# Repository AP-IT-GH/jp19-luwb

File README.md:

# Internet Of Things - *Location Ultra Wide Band*

## Angular

## API

**Teammembers**
* Hector Brasfalean
* Davy Cools
* Jens Peeters

## Summary
*Het lokaliseren van een robot/drone (indoor) door middel van Ultra Wide Band technologie. Dit gaan we visueel weergeven. We zullen de robot/drone ook op een autonome manier kunnen verplaatsen.*

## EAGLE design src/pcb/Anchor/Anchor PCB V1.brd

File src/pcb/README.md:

# PCB

In deze map verzamel je op een gestructueerde manier de bron bestanden voor het
PCB ontwerp.

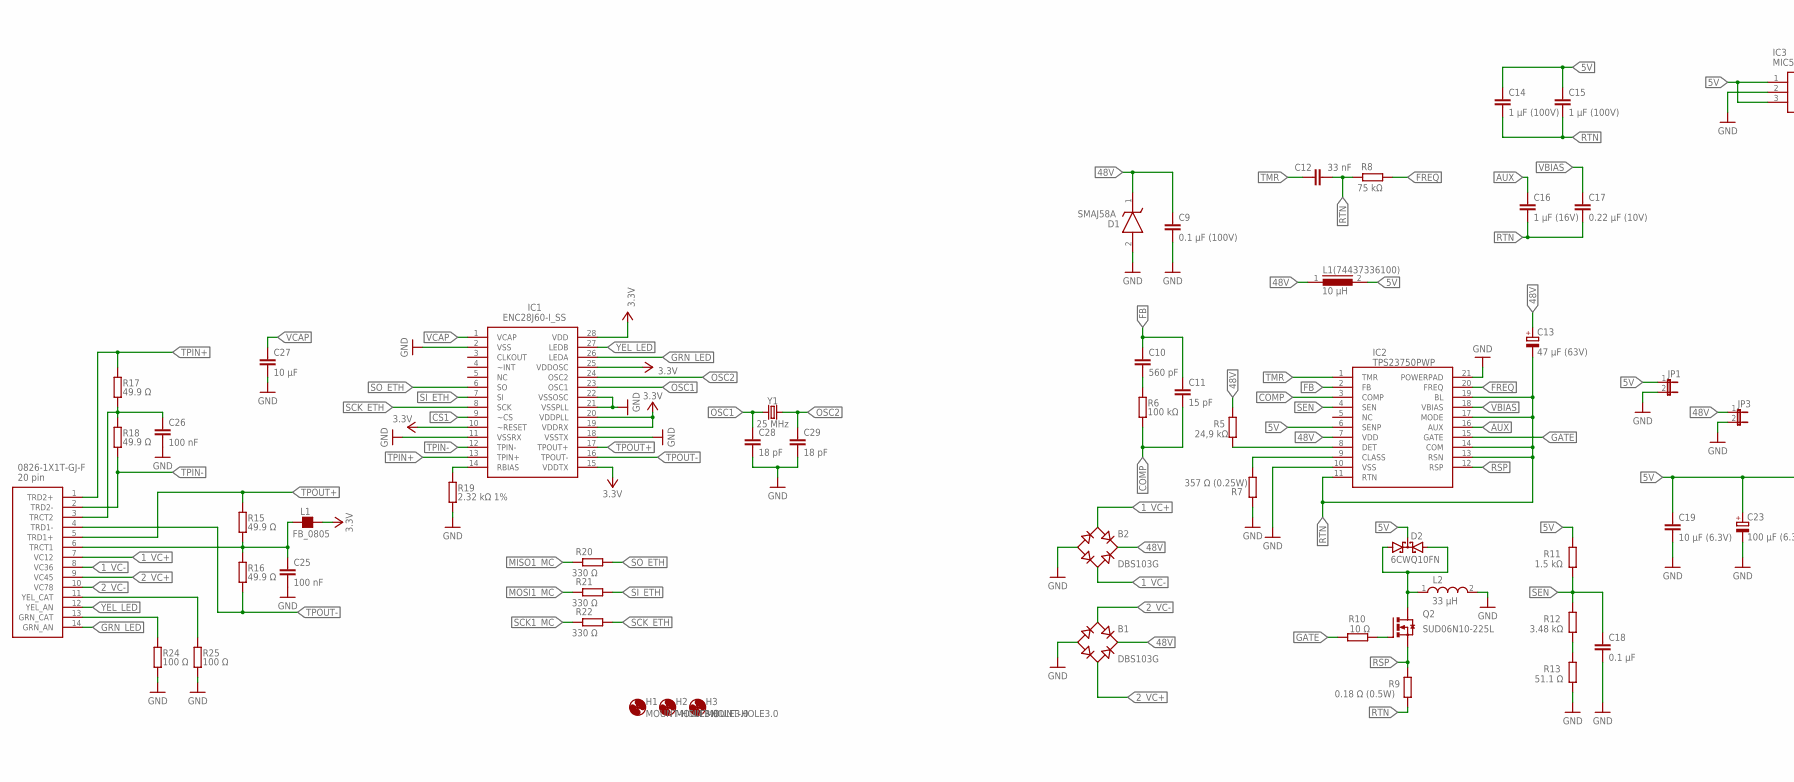
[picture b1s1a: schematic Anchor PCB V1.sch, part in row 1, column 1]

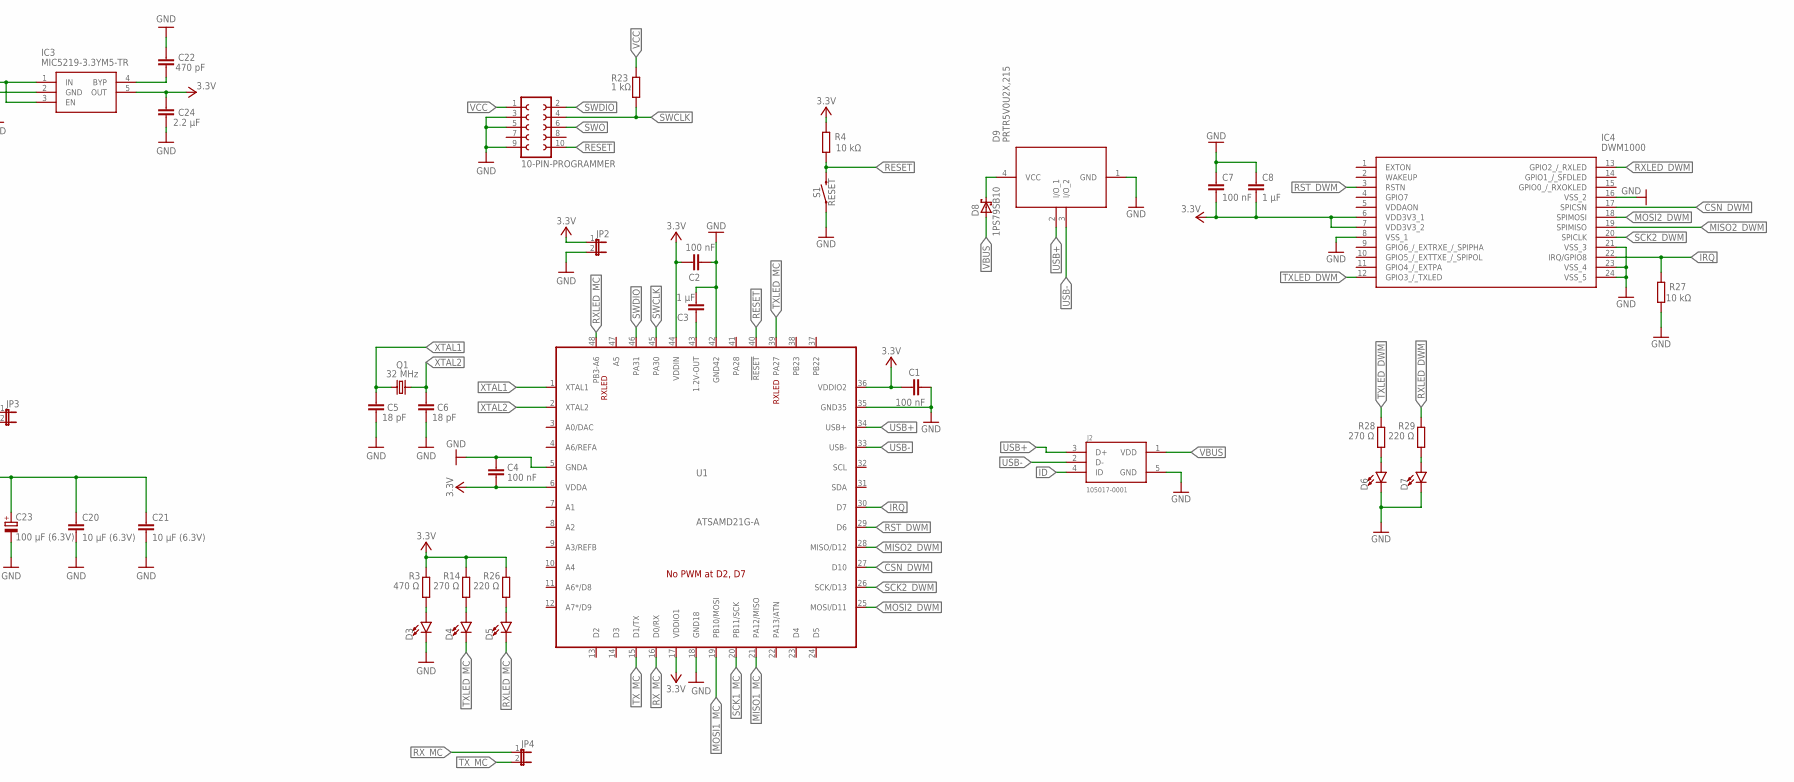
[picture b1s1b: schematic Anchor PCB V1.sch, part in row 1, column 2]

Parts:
10-PIN-PROGRAMMER: FE05-2
B1, B2: DBS103G; DBS
C1, C2, C4, C7, C25, C26: 100 nF; C0805
C3, C8: 1 µF; C0805
C5, C6, C28, C29: 18 pF; C0805
C9: 0.1 µF (100V); C0805
C10: 560 pF; C0805
C11: 15 pF; C0805
C12: 33 nF; C0805
C13: 47 µF (63V); E3,5-8
C14, C15: 1 µF (100V); C0805
C16: 1 µF (16V); C0805
C17: 0.22 µF (10V); C0805
C18: 0.1 µF; C0805
C19, C20, C21: 10 µF (6.3V); C0805
C22: 470 pF; C0805
C23: 100 µF (6.3V); UD-6,3X7,7_NICHICON
C24: 2.2 µF; C0805
C27: 10 µF; C0805
D1: SMAJ58A; DIOM5026X229N
D2: 6CWQ10FN; DPAK
D3: POWER; CHIP-LED0805
D4, D6: TX; CHIP-LED0805
D5, D7: RX; CHIP-LED0805
D8: 1PS79SB10; SOD523
D9: PRTR5V0U2X,215; SOT-143B
H1, H2, H3: MOUNT-HOLE3.0; 3,0
IC1: ENC28J60-I_SS; SOP65P780X200-28N
IC2: TPS23750PWP; SOP65P640X120-21N
IC3: MIC5219-3.3YM5-TR; SOT95P280X130-5N
IC4: DWM1000
J1: 0826-1X1T-GJ-F
J2: 105017-0001; MOLEX_105017-0001
JP1, JP2, JP3, JP4: JP1E; JP1
L1: FB_0805; L0805
L1(74437336100): 10 µH; DR73
L2: 33 µH; WE-PD_1260/1245/1280/1210
Q1: 32 MHz; ABS07
Q2: SUD06N10-225L; SOT223
R3: 470 Ω; R0805
R4, R27: 10 kΩ; M0805
R5: 24,9 kΩ; R0805
R6: 100 kΩ; R0805
R7: 357 Ω (0.25W); R0805
R8: 75 kΩ; R0805
R9: 0.18 Ω (0.5W); R2010
R10: 10 Ω; R0805
R11: 1.5 kΩ; R0805
R12: 3.48 kΩ; R0805
R13: 51.1 Ω; R0805
R14, R28: 270 Ω; R0805
R15, R16, R17, R18: 49.9 Ω; R0805
R19: 2.32 kΩ 1%; R0805
R20, R21, R22: 330 Ω; R0805
R23: 1 kΩ; R0805
R24, R25: 100 Ω; R0805
R26, R29: 220 Ω; R0805
S1: RESET; TACTILE_SWITCH_SMD_4.5MM
U1: ATSAMD21G-A; TQFP-48
Y1: 25 MHz; HC49UP

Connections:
1_VC+: B2.AC1, J1.7 (VC12)
1_VC-: B2.AC2, J1.8 (VC36)
2_VC+: B1.AC2, J1.9 (VC45)
2_VC-: B1.AC1, J1.10 (VC78)
5V: C14.1, C15.1, C19.1, C20.1, C21.1, C23.+, D2.4 (C), IC2.6 (SENP), IC3.1 (IN), IC3.3 (EN), JP1.1, L1(74437336100).2, R11.2
48V: B1.+, B2.+, C9.1, C13.+, D1.1 (K), IC2.7 (VDD), JP3.1, L1(74437336100).1, R5.2
AUX: C16.1, IC2.16 (AUX)
COMP: C11.2, IC2.3 (COMP), R6.2
COM_A_SHTKY: D2.1 (A1), D2.3 (A2), L2.1, Q2.4 (D)
CS1: IC1.9 (~CS)
CSN_DWM: IC4.17 (SPICSN), U1.27 (D10)
FB: C10.1, C11.1, IC2.2 (FB)
FREQ: IC2.20 (FREQ), R8.2
GATE: IC2.15 (GATE), R10.1
GND: 10-PIN-PROGRAMMER.3, 10-PIN-PROGRAMMER.5, 10-PIN-PROGRAMMER.9, B1.-, B2.-, C1.2, C2.2, C3.2, C4.2, C5.2, C6.2, C7.1, C8.1, C9.2, C18.2, C19.2, C20.2, C21.2, C22.1, C23.-, C24.2, C25.2, C26.2, C27.2, C28.2, C29.2, D1.2 (A), D3.C, D6.C, D7.C, D9.1 (GND), IC1.2 (VSS), IC1.11 (VSSRX), IC1.18 (VSSTX), IC1.21 (VSSPLL), IC1.22 (VSSOSC), IC2.10 (VSS), IC2.21 (POWERPAD), IC3.2 (GND), IC4.8 (VSS_1), IC4.16 (VSS_2), IC4.21 (VSS_3), IC4.23 (VSS_4), IC4.24 (VSS_5), J2.5 (GND), JP1.2, JP2.2, JP3.2, L2.2, R7.1, R13.1, R19.2, R24.2, R25.2, R27.1, S1.2 (1), S1.3 (1), U1.5 (GNDA), U1.18 (GND18), U1.35 (GND35), U1.42 (GND42)
GRN_CAT: J1.13 (GRN_CAT), R24.1
GRN_LED: IC1.26 (LEDA), J1.14 (GRN_AN)
ID: J2.4 (ID)
IRQ: IC4.22 (IRQ/GPIO8), R27.2, U1.30 (D7)
MISO1_MC: R20.1, U1.21 (PA12/MISO)
MISO2_DWM: IC4.19 (SPIMISO), U1.28 (MISO/D12)
MOSI1_MC: R21.1, U1.19 (PB10/MOSI)
MOSI2_DWM: IC4.18 (SPIMOSI), U1.25 (MOSI/D11)
unnamed: C3.1, U1.43 (1.2V-OUT)
unnamed: IC2.8 (DET), R5.1
unnamed: IC2.9 (CLASS), R7.2
unnamed: C25.1, J1.6 (TRCT1), L1.1, R15.2, R16.1
unnamed: C10.2, R6.1
unnamed: C26.1, J1.3 (TRCT2), R17.2, R18.1
unnamed: Q2.1 (G), R10.2
unnamed: IC1.14 (RBIAS), R19.1
unnamed: D3.A, R3.1
unnamed: R12.1, R13.2
unnamed: D4.A, R14.1
unnamed: D5.A, R26.1
unnamed: D6.A, R28.1
unnamed: D7.A, R29.1
unnamed: D8.1 (K), D9.4 (VCC)
unnamed: C22.2, IC3.4 (BYP)
OSC1: C28.1, IC1.23 (OSC1), Y1.1
OSC2: C29.1, IC1.24 (OSC2), Y1.2
RESET: 10-PIN-PROGRAMMER.10, R4.1, S1.1 (2), S1.4 (2), U1.40 (!RESET!)
RSP: IC2.12 (RSP), Q2.3 (S), R9.2
RST_DWM: IC4.3 (RSTN), U1.29 (D6)
RTN: C12.2, C13.-, C14.2, C15.2, C16.2, C17.2, IC2.11 (RTN), IC2.13 (RSN), IC2.14 (COM), IC2.17 (MODE), IC2.19 (BL), R8.1, R9.1
RXLED_DWM: IC4.13 (GPIO2_/_RXLED), R29.2
RXLED_MC: D5.C, U1.48 (PB3-A6)
RX_MC: JP4.1, U1.16 (D0/RX)
SCK1_MC: R22.1, U1.20 (PB11/SCK)
SCK2_DWM: IC4.20 (SPICLK), U1.26 (SCK/D13)
SCK_ETH: IC1.8 (SCK), R22.2
SEN: C18.1, IC2.4 (SEN), R11.1, R12.2
SI_ETH: IC1.7 (SI), R21.2
SO_ETH: IC1.6 (SO), R20.2
SWCLK: 10-PIN-PROGRAMMER.4, R23.1, U1.45 (PA30)
SWDIO: 10-PIN-PROGRAMMER.2, U1.46 (PA31)
SWO: 10-PIN-PROGRAMMER.6
TMR: C12.1, IC2.1 (TMR)
TPIN+: IC1.13 (TPIN+), J1.1 (TRD2+), R17.1
TPIN-: IC1.12 (TPIN-), J1.2 (TRD2-), R18.2
TPOUT+: IC1.17 (TPOUT+), J1.5 (TRD1+), R15.1
TPOUT-: IC1.16 (TPOUT-), J1.4 (TRD1-), R16.2
TXLED_DWM: IC4.12 (GPIO3_/_TXLED), R28.2
TXLED_MC: D4.C, U1.39 (PA27)
TX_MC: JP4.2, U1.15 (D1/TX)
USB+: D9.2 (I/O_1), J2.3 (D+), U1.34 (USB+)
USB-: D9.3 (I/O_2), J2.2 (D-), U1.33 (USB-)
VBIAS: C17.1, IC2.18 (VBIAS)
VBUS: D8.2 (A), J2.1 (VDD)
VCAP: C27.1, IC1.1 (VCAP)
VCC: 10-PIN-PROGRAMMER.1, C1.1, C2.1, C4.1, C7.2, C8.2, C24.1, IC1.10 (~RESET), IC1.15 (VDDTX), IC1.19 (VDDRX), IC1.20 (VDDPLL), IC1.25 (VDDOSC), IC1.28 (VDD), IC3.5 (OUT), IC4.6 (VDD3V3_1), IC4.7 (VDD3V3_2), JP2.1, L1.2, R3.2, R4.2, R14.2, R23.2, R26.2, U1.6 (VDDA), U1.17 (VDDIO1), U1.36 (VDDIO2), U1.44 (VDDIN)
XTAL1: C5.1, Q1.2, U1.1 (XTAL1)
XTAL2: C6.1, Q1.1, U1.2 (XTAL2)
YEL_CAT: J1.11 (YEL_CAT), R25.1
YEL_LED: IC1.27 (LEDB), J1.12 (YEL_AN)

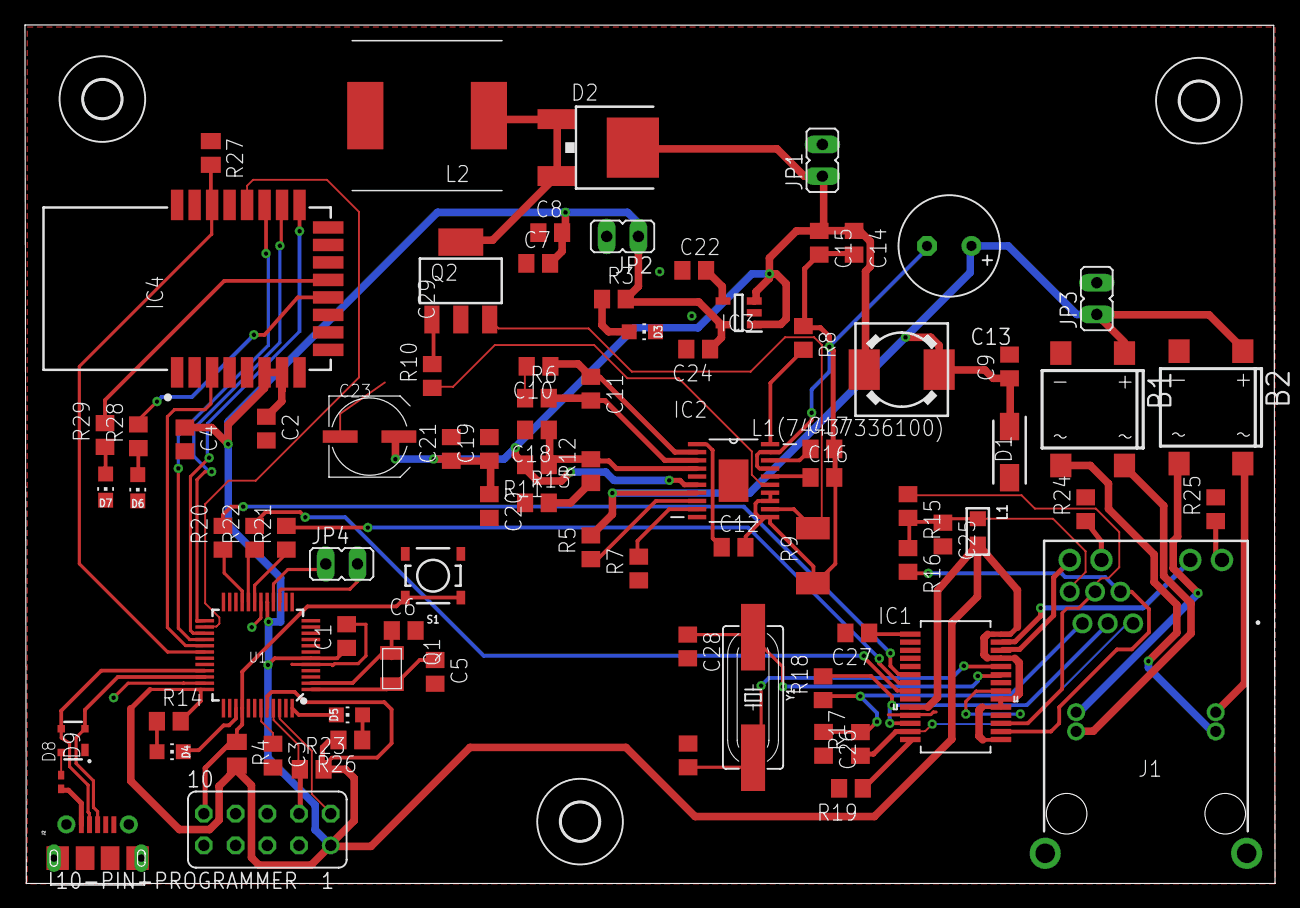
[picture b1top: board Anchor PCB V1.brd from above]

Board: 2 copper layers, 100.1 x 68.7 mm, 89 parts (0 on the bottom side), 72 nets.

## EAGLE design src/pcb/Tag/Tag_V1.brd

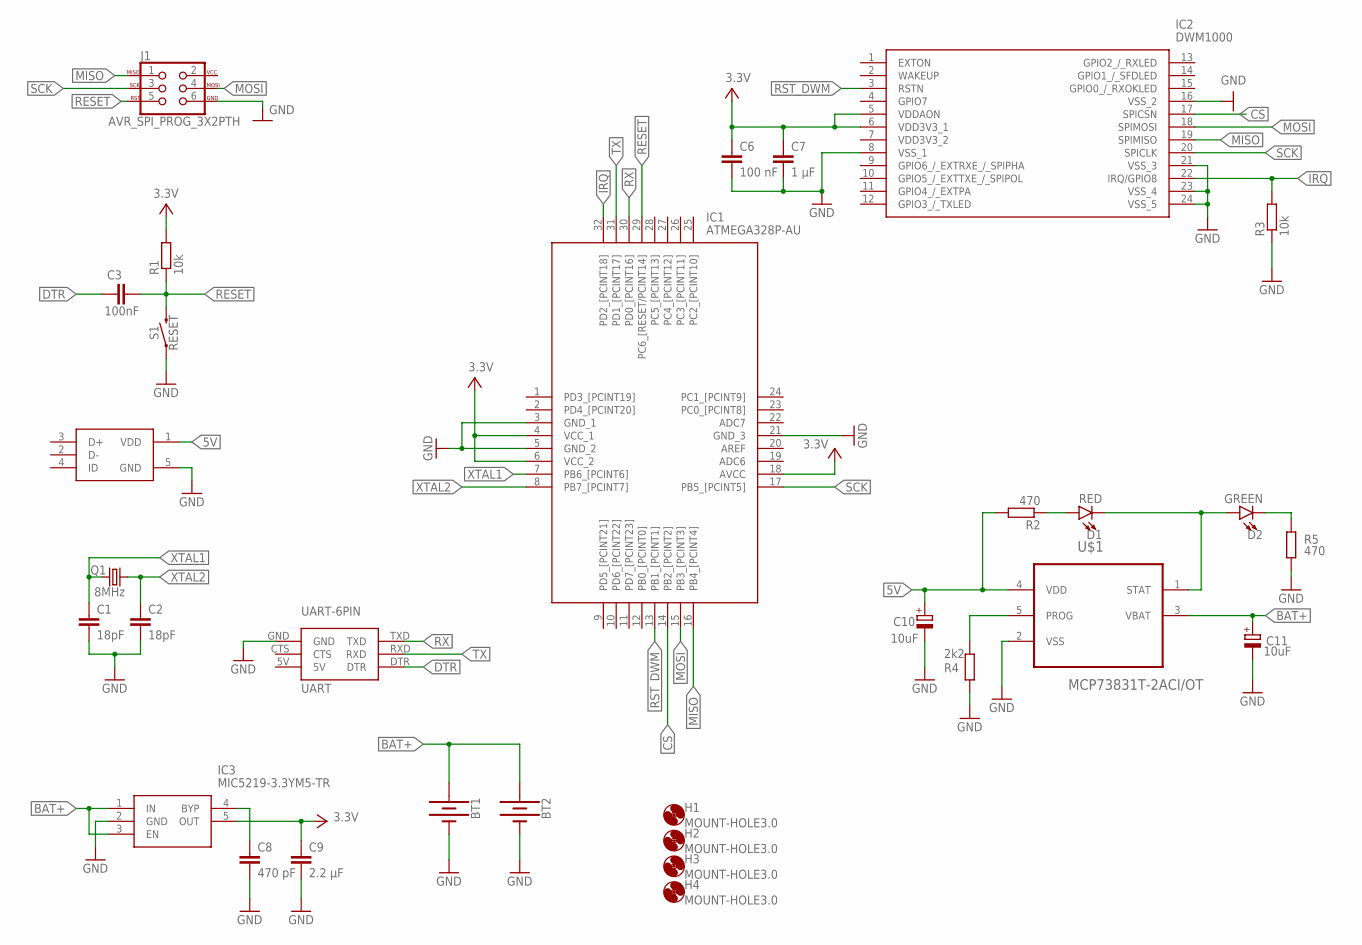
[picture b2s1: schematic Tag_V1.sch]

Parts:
BT1, BT2: BATTERY-18650; BATTERY_18650-HOLDER
C1, C2: 18pF; C0805
C3: 100nF; C0805
C6: 100 nF; C0805
C7: 1 µF; C0805
C8: 470 pF; C0805
C9: 2.2 µF; C0805
C10, C11: 10uF; E2,5-7
D1: RED; LED-1206
D2: GREEN; LED-1206
H1, H2, H3, H4: MOUNT-HOLE3.0; 3,0
IC1: ATMEGA328P-AU; QFP80P900X900X120-32N
IC2: DWM1000
IC3: MIC5219-3.3YM5-TR; SOT95P280X130-5N
J1: AVR_SPI_PROG_3X2PTH; 2X3
Q1: 8MHz; HC49UP
R1, R3: 10k; R0805
R2, R5: 470; R0805
R4: 2k2; R0805
S1: RESET; TACTILE_SWITCH_PTH_6.0MM
U1: 105017-0001; MOLEX_105017-0001
U$1: MCP73831T-2ACI/OT; SOT95P280X145-5N
U$2: UART-6PIN

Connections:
3.3V: C6.1, C7.1, C9.1, IC1.4 (VCC_1), IC1.6 (VCC_2), IC1.18 (AVCC), IC2.5 (VDDAON), IC2.6 (VDD3V3_1), IC3.5 (OUT), R1.2
5V: C10.+, R2.2, U1.1 (VDD), U$1.4 (VDD)
BAT+: BT1.PWR@1 (+), BT2.PWR@1 (+), C11.+, IC3.1 (IN), IC3.3 (EN), U$1.3 (VBAT)
CS: IC1.14 (PB2_[PCINT2]), IC2.17 (SPICSN)
DTR: C3.1, U$2.DTR
GND: BT1.GND@1 (-), BT2.GND@1 (-), C1.2, C2.2, C6.2, C7.2, C8.2, C9.2, C10.-, C11.-, IC1.3 (GND_1), IC1.5 (GND_2), IC1.21 (GND_3), IC2.8 (VSS_1), IC2.16 (VSS_2), IC2.21 (VSS_3), IC2.23 (VSS_4), IC2.24 (VSS_5), IC3.2 (GND), J1.6, R3.1, R4.2, R5.2, S1.1, U1.5 (GND), U$1.2 (VSS), U$2.GND
IRQ: IC1.32 (PD2_[PCINT18]), IC2.22 (IRQ/GPIO8), R3.2
MISO: IC1.16 (PB4_[PCINT4]), IC2.19 (SPIMISO), J1.1
MOSI: IC1.15 (PB3_[PCINT3]), IC2.18 (SPIMOSI), J1.4
unnamed: D1.C, D2.A, U$1.1 (STAT)
unnamed: D1.A, R2.1
unnamed: C8.1, IC3.4 (BYP)
unnamed: D2.C, R5.1
unnamed: R4.1, U$1.5 (PROG)
RESET: C3.2, IC1.29 (PC6_[RESET/PCINT14]), J1.5, R1.1, S1.3 (2)
RST_DWM: IC1.13 (PB1_[PCINT1]), IC2.3 (RSTN)
RX: IC1.30 (PD0_[PCINT16]), U$2.TXD
SCK: IC1.17 (PB5_[PCINT5]), IC2.20 (SPICLK), J1.3
TX: IC1.31 (PD1_[PCINT17]), U$2.RXD
XTAL1: C1.1, IC1.7 (PB6_[PCINT6]), Q1.1
XTAL2: C2.1, IC1.8 (PB7_[PCINT7]), Q1.2

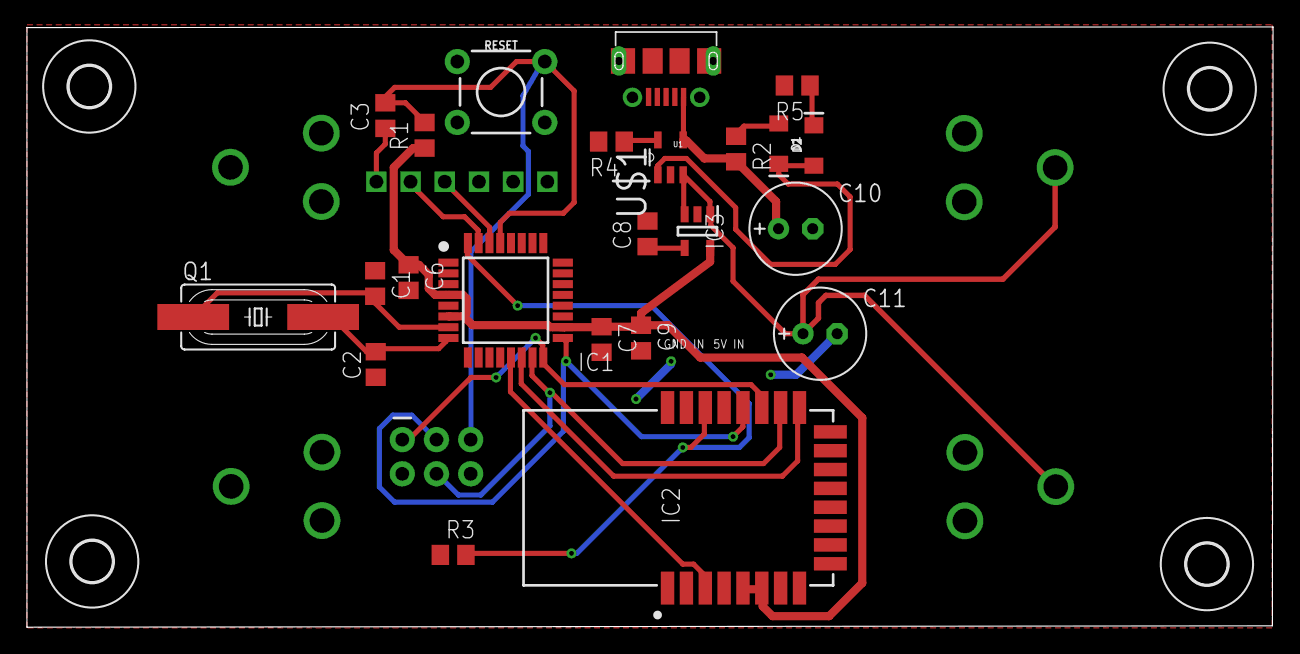
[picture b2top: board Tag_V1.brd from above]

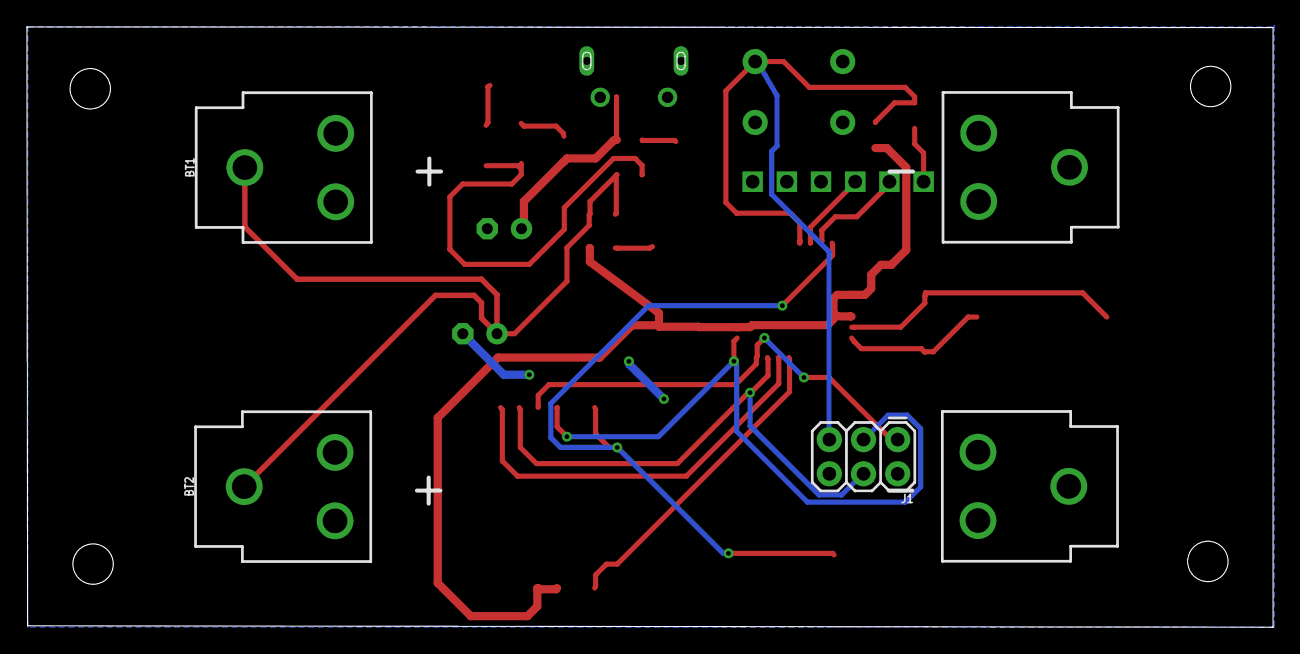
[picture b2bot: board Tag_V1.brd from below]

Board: 2 copper layers, 92.6 x 44.6 mm, 31 parts (3 on the bottom side), 21 nets.

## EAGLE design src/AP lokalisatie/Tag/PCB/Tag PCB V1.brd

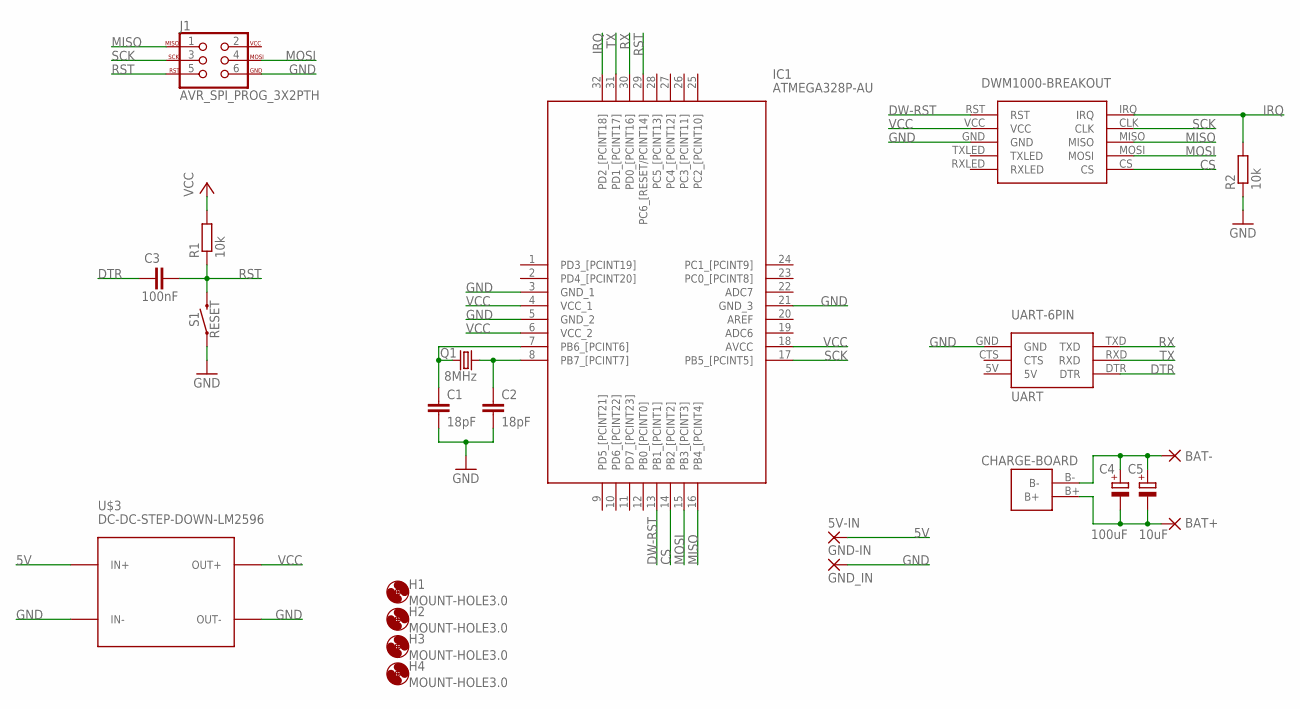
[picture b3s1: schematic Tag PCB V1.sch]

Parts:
5V-IN: 2,15/1,0
BAT+: 2,15/1,0
BAT-: 2,15/1,0
C1, C2: 18pF; C0805
C3: 100nF; C0805
C4: 100uF; E3,5-8
C5: 10uF; E2,5-7
GND-IN: GND_IN; 2,15/1,0
H1, H2, H3, H4: MOUNT-HOLE3.0; 3,0
IC1: ATMEGA328P-AU; QFP80P900X900X120-32N
J1: AVR_SPI_PROG_3X2PTH; 2X3
Q1: 8MHz; HC49UP
R1, R2: 10k; R0805
S1: RESET; TACTILE_SWITCH_PTH_6.0MM
U$1: DWM1000-BREAKOUT
U$2: UART-6PIN
U$3: DC-DC-STEP-DOWN-LM2596
U$4: 18650-CHARGE-5V-OUT

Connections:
5V: 5V-IN.1, U$3.IN+
CS: IC1.14 (PB2_[PCINT2]), U$1.CS
DTR: C3.1, U$2.DTR
DW-RST: IC1.13 (PB1_[PCINT1]), U$1.RST
GND: C1.2, C2.2, GND-IN.1, IC1.3 (GND_1), IC1.5 (GND_2), IC1.21 (GND_3), J1.6, R2.1, S1.1, U$1.GND, U$2.GND, U$3.IN-, U$3.OUT-
IRQ: IC1.32 (PD2_[PCINT18]), R2.2, U$1.IRQ
MISO: IC1.16 (PB4_[PCINT4]), J1.1, U$1.MISO
MOSI: IC1.15 (PB3_[PCINT3]), J1.4, U$1.MOSI
unnamed: BAT-.1, C4.+, C5.+, U$4.B-
unnamed: BAT+.1, C4.-, C5.-, U$4.B+
unnamed: C2.1, IC1.8 (PB7_[PCINT7]), Q1.2
unnamed: C1.1, IC1.7 (PB6_[PCINT6]), Q1.1
RST: C3.2, IC1.29 (PC6_[RESET/PCINT14]), J1.5, R1.1, S1.3 (2)
RX: IC1.30 (PD0_[PCINT16]), U$2.TXD
SCK: IC1.17 (PB5_[PCINT5]), J1.3, U$1.CLK
TX: IC1.31 (PD1_[PCINT17]), U$2.RXD
VCC: IC1.4 (VCC_1), IC1.6 (VCC_2), IC1.18 (AVCC), R1.2, U$1.VCC, U$3.OUT+

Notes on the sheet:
CHARGE-BOARD

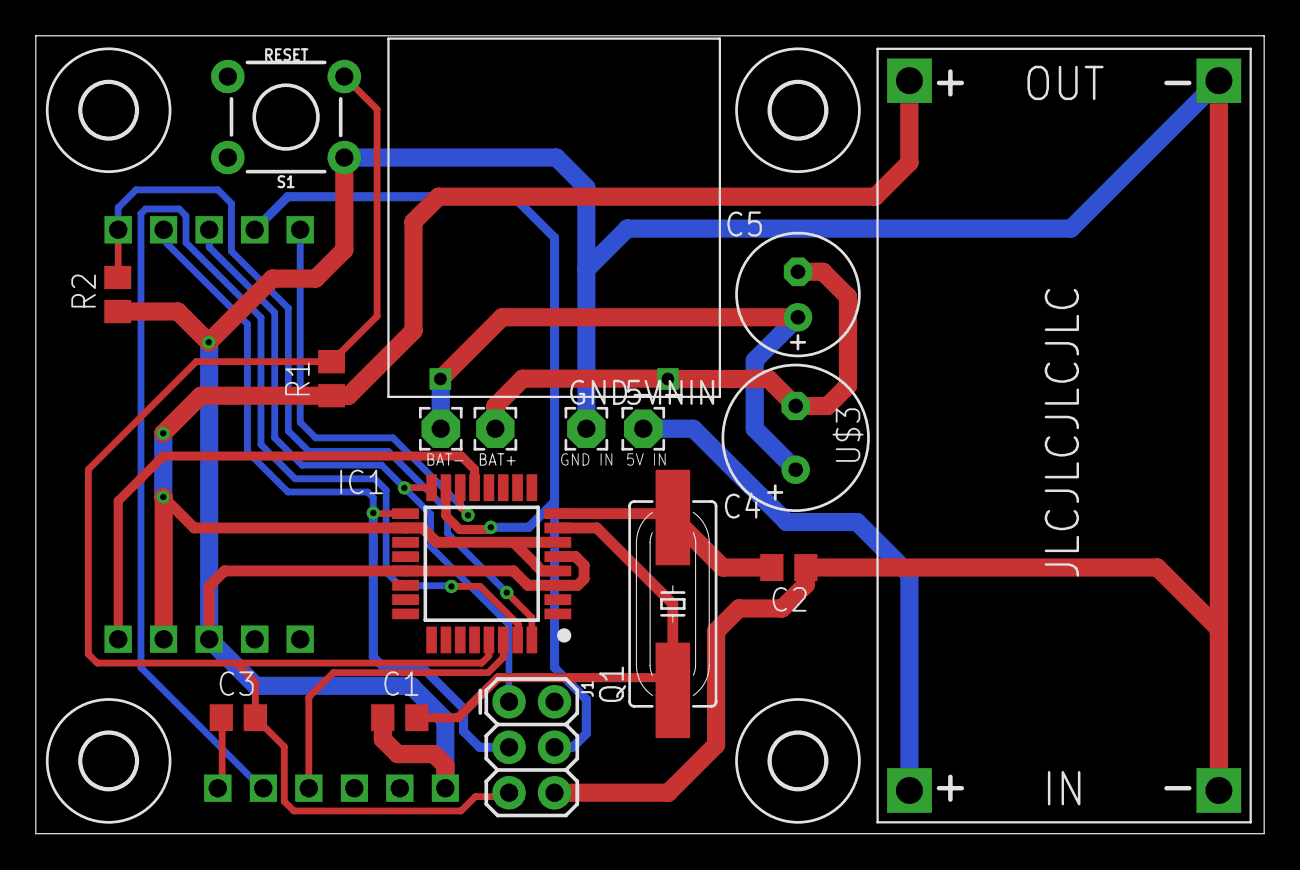
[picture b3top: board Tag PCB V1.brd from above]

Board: 2 copper layers, 68.6 x 44.5 mm, 23 parts (0 on the bottom side), 17 nets.

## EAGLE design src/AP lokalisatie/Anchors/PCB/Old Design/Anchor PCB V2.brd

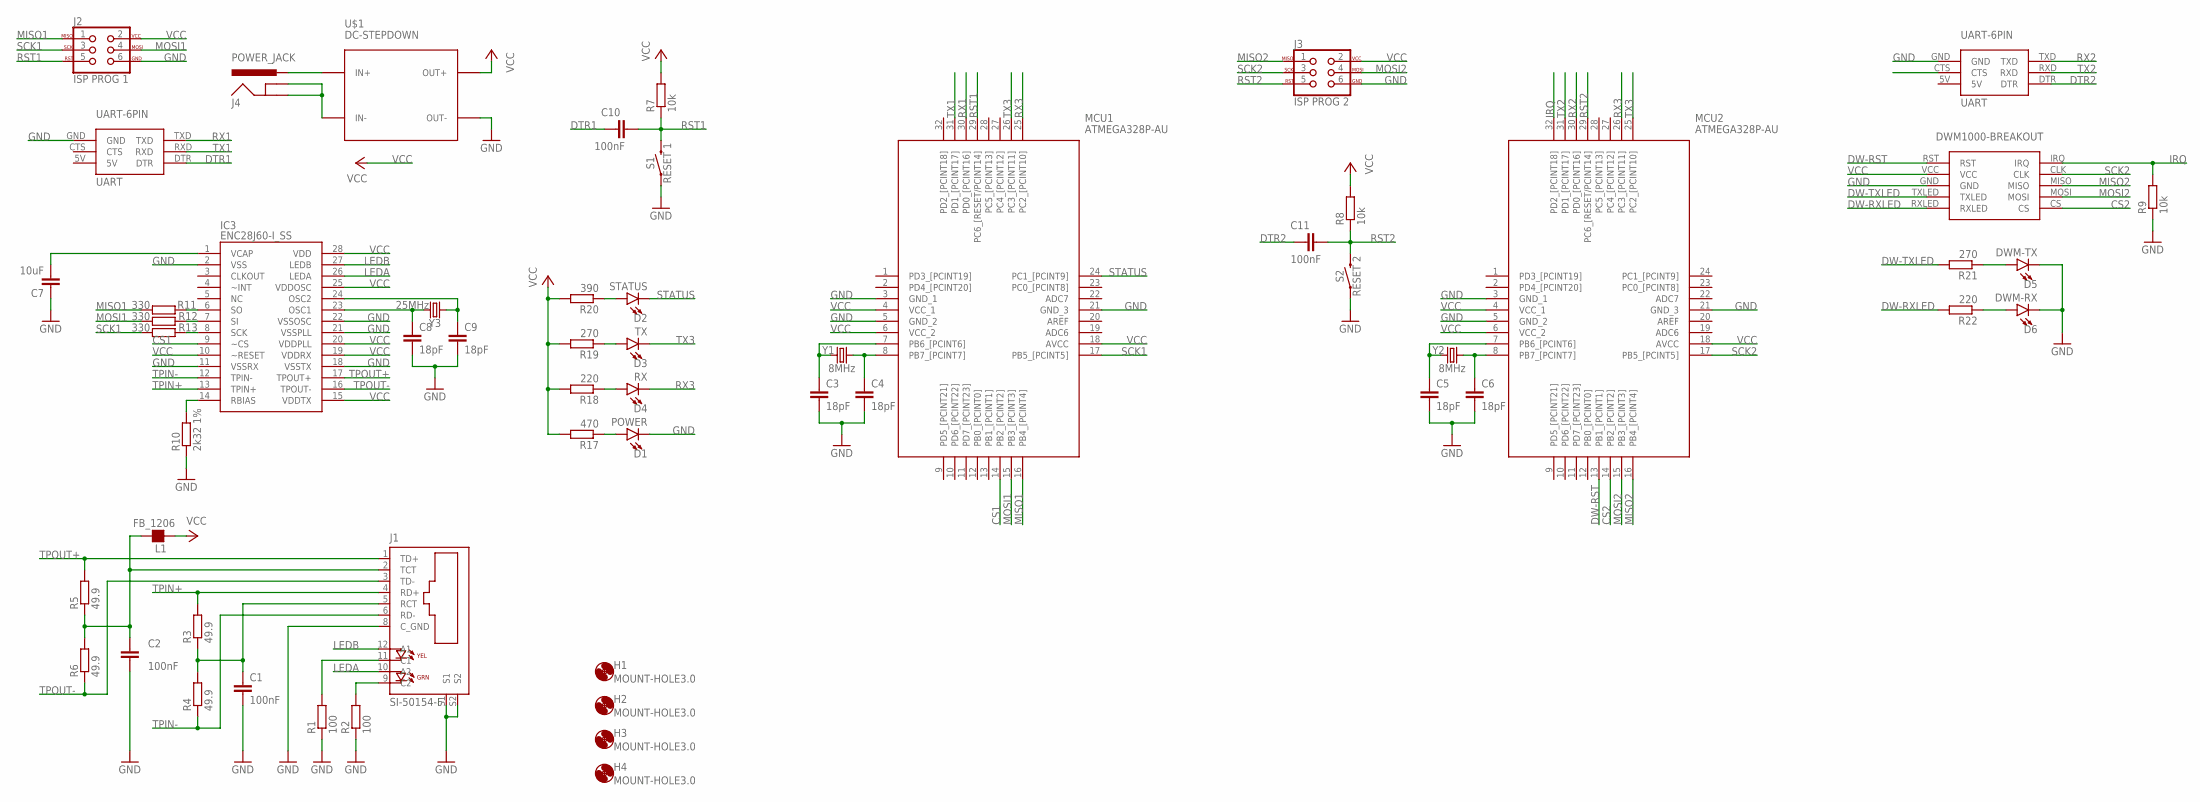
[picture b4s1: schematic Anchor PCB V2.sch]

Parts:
C1, C2, C10, C11: 100nF; C0805
C3, C4, C5, C6, C8, C9: 18pF; C0805
C7: 10uF; C0805
D1: POWER; LED-1206
D2: STATUS; LED-1206
D3: TX; LED-1206
D4: RX; LED-1206
D5: DWM-TX; LED-1206
D6: DWM-RX; LED-1206
H1, H2, H3, H4: MOUNT-HOLE3.0; 3,0
IC3: ENC28J60-I_SS; SOP65P780X200-28N
J1: SI-50154-F; STEWART_SI-50154-F
J2: ISP PROG 1; 2X3
J3: ISP PROG 2; 2X3
J4: POWER_JACK; POWER_JACK_PTH
L1: FB_1206; L1206
MCU1, MCU2: ATMEGA328P-AU; QFP80P900X900X120-32N
R1, R2: 100; R0805
R3, R4, R5, R6: 49.9; R1206
R7, R8, R9: 10k; R0805
R10: 2k32 1%; R1206
R11, R12, R13: 330; R0805
R17: 470; R1206
R18, R22: 220; R1206
R19, R21: 270; R1206
R20: 390; R1206
S1: RESET 1; TACTILE_SWITCH_PTH_6.0MM
S2: RESET 2; TACTILE_SWITCH_PTH_6.0MM
U$1: DC-STEPDOWN; DC-DC-STEP-DOWN-LM2596
U$2: DWM1000; DWM1000-BREAKOUT
UART1: UART1; UART-6PIN
UART2: UART2; UART-6PIN
Y1, Y2: 8MHz; HC49UP
Y3: 25MHz; HC49UP

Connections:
CS1: IC3.9 (~CS), MCU1.14 (PB2_[PCINT2])
CS2: MCU2.14 (PB2_[PCINT2]), U$2.CS
DTR1: C10.1, UART1.DTR
DTR2: C11.1, UART2.DTR
DW-RST: MCU2.13 (PB1_[PCINT1]), U$2.RST
DW-RXLED: R22.2, U$2.RXLED
DW-TXLED: R21.2, U$2.TXLED
GND: C1.2, C2.2, C3.2, C4.2, C5.2, C6.2, C7.1, C8.2, C9.2, D1.C, D5.C, D6.C, IC3.2 (VSS), IC3.11 (VSSRX), IC3.18 (VSSTX), IC3.21 (VSSPLL), IC3.22 (VSSOSC), J1.8 (C_GND), J1.S1, J1.S2, J2.6, J3.6, MCU1.3 (GND_1), MCU1.5 (GND_2), MCU1.21 (GND_3), MCU2.3 (GND_1), MCU2.5 (GND_2), MCU2.21 (GND_3), R1.1, R2.1, R9.1, R10.1, S1.1, S2.1, U$1.OUT-, U$2.GND, UART1.GND, UART2.GND
IN+: J4.PWR, U$1.IN+
IN-: J4.GND, J4.GNDBREAK, U$1.IN-
IRQ: MCU2.32 (PD2_[PCINT18]), R9.2, U$2.IRQ
LEDA: IC3.26 (LEDA), J1.10 (A2)
LEDB: IC3.27 (LEDB), J1.12 (A1)
MISO1: J2.1, MCU1.16 (PB4_[PCINT4]), R11.2
MISO2: J3.1, MCU2.16 (PB4_[PCINT4]), U$2.MISO
MOSI1: J2.4, MCU1.15 (PB3_[PCINT3]), R12.2
MOSI2: J3.4, MCU2.15 (PB3_[PCINT3]), U$2.MOSI
unnamed: J1.11 (C1), R1.2
unnamed: J1.9 (C2), R2.2
unnamed: C3.1, MCU1.7 (PB6_[PCINT6]), Y1.2
unnamed: C4.1, MCU1.8 (PB7_[PCINT7]), Y1.1
unnamed: C5.1, MCU2.7 (PB6_[PCINT6]), Y2.1
unnamed: C6.1, MCU2.8 (PB7_[PCINT7]), Y2.2
unnamed: C7.2, IC3.1 (VCAP)
unnamed: IC3.14 (RBIAS), R10.2
unnamed: C8.1, IC3.23 (OSC1), Y3.2
unnamed: C9.1, IC3.24 (OSC2), Y3.1
unnamed: IC3.6 (SO), R11.1
unnamed: C1.1, J1.5 (RCT), R3.1, R4.2
unnamed: C2.1, J1.2 (TCT), L1.2, R5.1, R6.2
unnamed: IC3.7 (SI), R12.1
unnamed: IC3.8 (SCK), R13.1
unnamed: D5.A, R21.1
unnamed: D4.A, R18.1
unnamed: D2.A, R20.1
unnamed: D3.A, R19.1
unnamed: D6.A, R22.1
unnamed: D1.A, R17.1
RST1: C10.2, J2.5, MCU1.29 (PC6_[RESET/PCINT14]), R7.1, S1.3 (2)
RST2: C11.2, J3.5, MCU2.29 (PC6_[RESET/PCINT14]), R8.1, S2.3 (2)
RX1: MCU1.30 (PD0_[PCINT16]), UART1.TXD
RX2: MCU2.30 (PD0_[PCINT16]), UART2.TXD
RX3: D4.C, MCU1.25 (PC2_[PCINT10]), MCU2.26 (PC3_[PCINT11])
SCK1: J2.3, MCU1.17 (PB5_[PCINT5]), R13.2
SCK2: J3.3, MCU2.17 (PB5_[PCINT5]), U$2.CLK
STATUS: D2.C, MCU1.24 (PC1_[PCINT9])
TPIN+: IC3.13 (TPIN+), J1.4 (RD+), R3.2
TPIN-: IC3.12 (TPIN-), J1.6 (RD-), R4.1
TPOUT+: IC3.17 (TPOUT+), J1.1 (TD+), R5.2
TPOUT-: IC3.16 (TPOUT-), J1.3 (TD-), R6.1
TX1: MCU1.31 (PD1_[PCINT17]), UART1.RXD
TX2: MCU2.31 (PD1_[PCINT17]), UART2.RXD
TX3: D3.C, MCU1.26 (PC3_[PCINT11]), MCU2.25 (PC2_[PCINT10])
VCC: IC3.10 (~RESET), IC3.15 (VDDTX), IC3.19 (VDDRX), IC3.20 (VDDPLL), IC3.25 (VDDOSC), IC3.28 (VDD), J2.2, J3.2, L1.1, MCU1.4 (VCC_1), MCU1.6 (VCC_2), MCU1.18 (AVCC), MCU2.4 (VCC_1), MCU2.6 (VCC_2), MCU2.18 (AVCC), R7.2, R8.2, R17.2, R18.2, R19.2, R20.2, U$1.OUT+, U$2.VCC

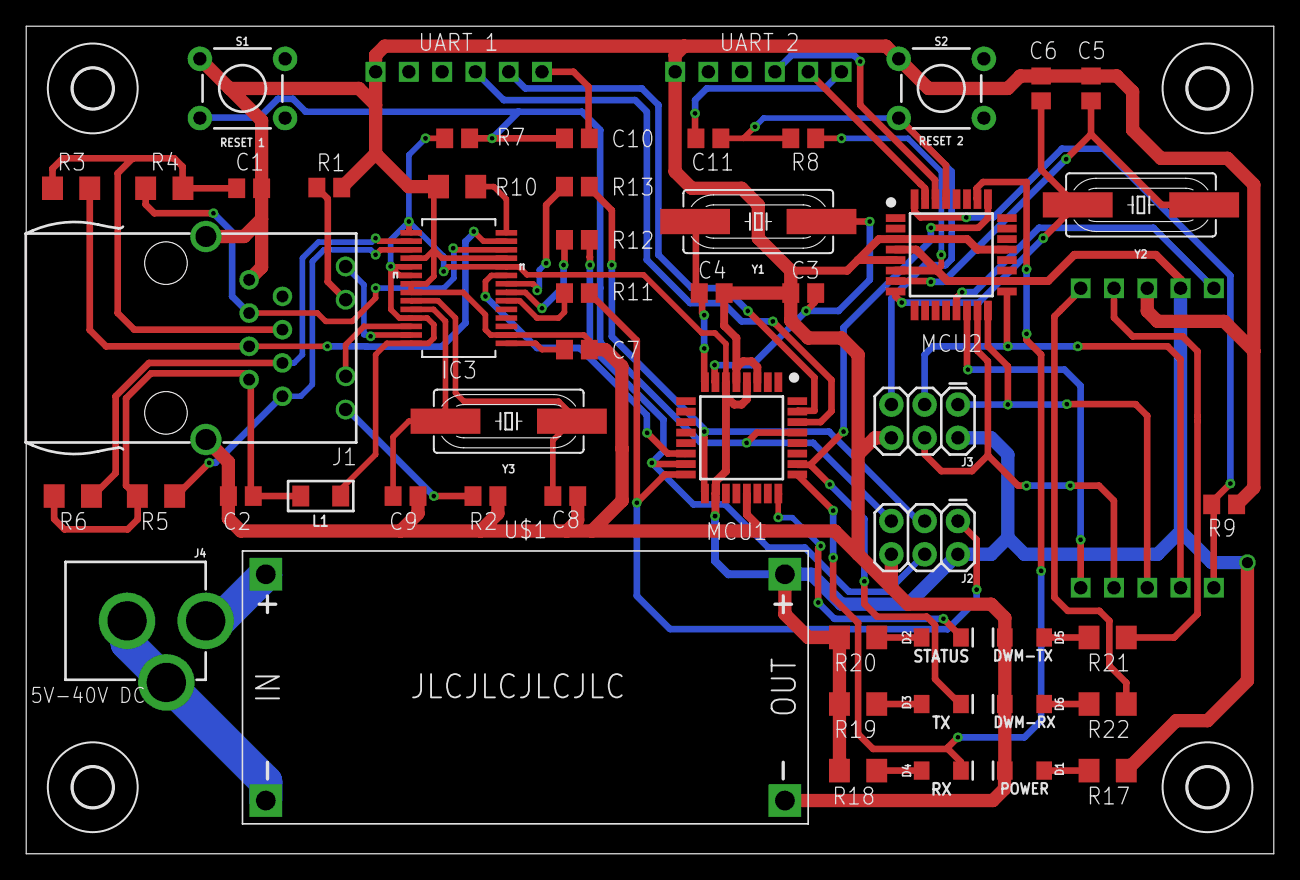
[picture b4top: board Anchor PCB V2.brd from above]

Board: 2 copper layers, 95.2 x 63.2 mm, 57 parts (0 on the bottom side), 54 nets.

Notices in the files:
parts and their libraries:
SparkFun-Connectors: Licensing: Creative Commons ShareAlike 4.0 International - https://creativecommons.org/licenses/by-sa/4.0
rc-master-smd: Copyright (C) 2007, Bob Starr
wurth_elektronik_passive_rev16d: Copyright: Würth Elektronik
